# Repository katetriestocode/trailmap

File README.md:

# trailmap
trailmap is a long lasting, gps enabled, e-ink trail map viewer! equipped with temperature, humidity, magnetometer, altitude and gps, it lets the user choose and follow hiking trails like a map! with a usb-c rechargeable lipo battery, it will provide a long lasting and wifi-scarcity proof solution to digital maps :D

this is the working version! (disclaimer: no antenna as it has not delivered yet, so manual gps coords insertion for now!)

provisional 3d model:

pcb:

schematic:

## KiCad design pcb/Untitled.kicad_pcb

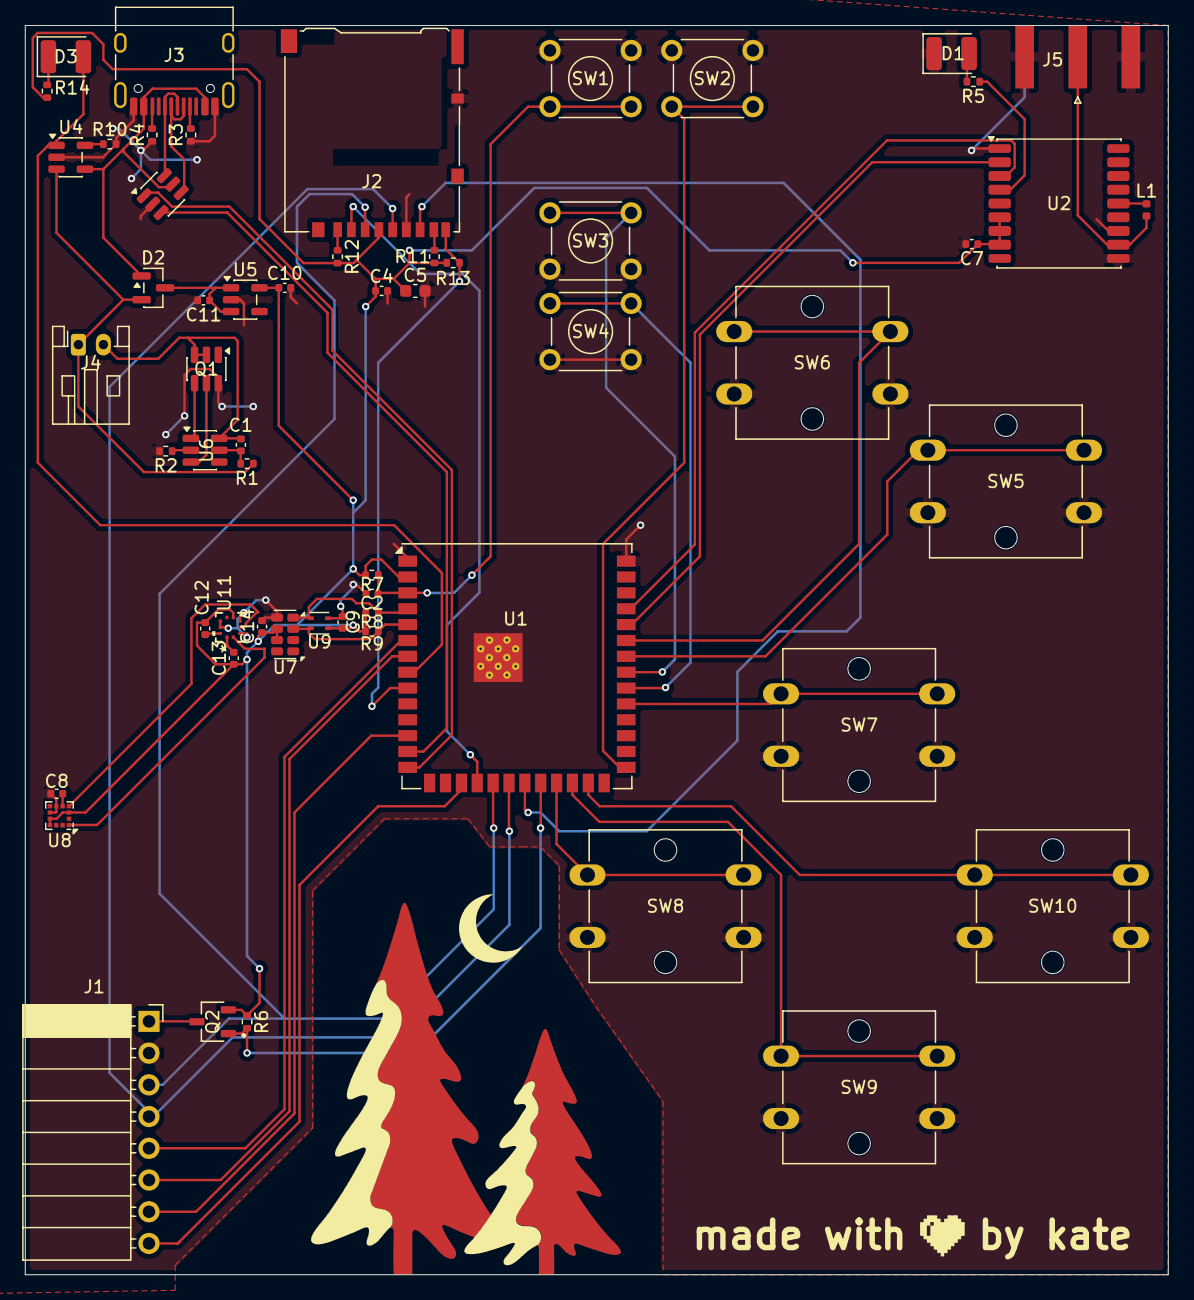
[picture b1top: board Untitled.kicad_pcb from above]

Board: 2 copper layers, 91.5 x 100.0 mm, 57 parts (0 on the bottom side), 53 nets.

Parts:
C1, C4, C7, C9, C14: 0.1uF; C_0402_1005Metric
C2, C10, C11: 1uF; C_0402_1005Metric
C5: 10uF; C_0603_1608Metric
C8: 220nF; C_0402_1005Metric
C12, C13: 0.1UF; C_0402_1005Metric
D1, D3: LED; LED_1210_3225Metric
D2: BAT54C; SOT-23
J1: Conn_01x08_Socket; PinSocket_1x08_P2.54mm_Horizontal
J2: Micro_SD_Card_Det1; microSD_HC_Hirose_DM3AT-SF-PEJM5
J3: USB_C_Receptacle_USB2.0_14P; USB_C_Receptacle_HRO_TYPE-C-31-M-12
J4: Conn_01x02; JST_PH_S2B-PH-K_1x02_P2.00mm_Horizontal
J5: Conn_Coaxial; SMA_Amphenol_132289_EdgeMount
L1: 27nH; L_0402_1005Metric
Q1: FS8205A; SOT-23-6
Q2: AO3407A; SOT95P280X125-3N
R1: 100; R_0402_1005Metric
R2, R5: 1k; R_0402_1005Metric
R3, R4: 5.1k; R_0402_1005Metric
R6, R7, R11, R12, R13: 10k; R_0402_1005Metric
R8, R9: 4.7k; R_0402_1005Metric
R10, R14: 2k; R_0402_1005Metric
SW1: reset; SW_TH_Tactile_Omron_B3F-100x
SW2: boot; SW_TH_Tactile_Omron_B3F-100x
SW3, SW4: SW_Push; SW_TH_Tactile_Omron_B3F-100x
SW5, SW6, SW7, SW8, SW9, SW10: SW_Push; SW_SPST_Omron_B3F-40xx
U1: ESP32-S3-WROOM-1; ESP32-S3-WROOM-1U
U2: MAX-M10S; ublox_MAX
U3: USBLC6-2SC6; SOT-23-6
U4: MCP73831-2-MC; SOT-23-5
U5: AP2112K-3.3; SOT-23-5
U6: DW01A; SOT-23-6
U7: RV-3028-C7; MicroCrystal_C7_SON-8_1.5x3.2mm_P0.9mm
U8: LIS2MDL; LGA-12_2x2mm_P0.5mm
U9: SHT4x; Sensirion_DFN-4_1.5x1.5mm_P0.8mm_SHT4x_NoCentralPad
U11: BMP390; 10LGA_2X2X0p75_BOS

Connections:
+3V3: C4.1, C5.1, C7.1, C9.2, C10.1, C12.1, C13.1, C14.1, J2.4 (VDD), Q2.2, R6.1, R7.1, R8.2, R9.2, R11.2, R12.2, R13.1, R14.1, U1.2 (3V3), U2.6 (V_BCKP), U2.7 (VCC_IO), U2.8 (VCC), U5.5 (VOUT), U7.6 (VBACKUP), U7.7 (VDD), U8.3 (~CS), U8.9 (Vdd), U8.10 (Vdd_IO), U9.3 (VDD), U11.6 (CSB)
+5V: D2.1, J3.A4 (VBUS), J3.A9 (VBUS), J3.B4 (VBUS), J3.B9 (VBUS), U3.5 (VBUS), U4.4 (V_{DD})
BAT+: D2.2, J4.1, R1.1, U4.3 (V_{BAT})
BAT-: C1.2, J4.2, Q1.2, Q1.3, U6.6 (GND)
GND: C2.2, C4.2, C5.2, C7.2, C8.2, C9.1, C10.2, C11.2, C14.2, D1.1 (K), J1.2, J2.6 (VSS), J2.10 (SHIELD), J3.A1 (GND), J3.A12 (GND), J3.B1 (GND), J3.B12 (GND), J5.2 (Ext), Q1.6, R2.2, R3.1, R4.1, R10.2, SW1.1, SW2.1, SW3.2, SW4.2, SW5.2, SW6.2, SW7.2, SW8.2, SW9.2, SW10.2, U1.1 (GND), U1.40 (GND), U1.41 (GND), U2.1 (GND), U2.10 (GND), U2.12 (GND), U3.2 (GND), U4.2 (V_{SS}), U5.2 (GND), U7.5 (VSS), U8.6 (GND), U8.8 (GND), U9.4 (VSS), U11.3 (VSS), U11.5 (SDO), U11.8 (VSS), U11.9 (VSS)
GPS_TO_MCU: U1.36 (RXD0), U2.2 (TXD)
IO06: J1.5, U1.6 (IO6)
IO07: J1.6, U1.7 (IO7)
IO08: J1.7, U1.12 (IO8)
IO09: J1.8, U1.17 (IO9)
IO10: J2.2 (DAT3/CD), U1.18 (IO10)
IO11: J1.3, J2.3 (CMD), U1.19 (IO11)
IO12: J1.4, J2.5 (CLK), U1.20 (IO12)
IO13: J2.7 (DAT0), U1.21 (IO13)
IO14: Q2.1, R6.2, U1.22 (IO14)
IO15: D3.2 (A), U1.8 (IO15), U4.1 (STAT)
IO16: J2.9 (DET), R13.2, U1.9 (IO16)
IO21: SW8.1, U1.23 (IO21)
IO38: SW7.1, U1.31 (IO38)
IO39: SW4.1, U1.32 (IO39)
IO40: SW3.1, U1.33 (IO40)
IO41: SW5.1, U1.34 (IO41)
IO42: SW6.1, U1.35 (IO42)
IO47: SW9.1, U1.24 (IO47)
IO48: SW10.1, U1.25 (IO48)
MCU_TO_GPS: U1.37 (TXD0), U2.3 (RXD)
unnamed: D1.2 (A), R5.2
unnamed: D3.1 (K), R14.2
unnamed: J1.1, Q2.3
unnamed: J2.8 (DAT1), R11.1
unnamed: J2.1 (DAT2), R12.1
unnamed: J3.A5 (CC1), R3.2
unnamed: J3.B5 (CC2), R4.2
unnamed: J3.A6 (D+), J3.B6 (D+), U3.6 (I/O1)
unnamed: J3.A7 (D-), J3.B7 (D-), U3.4 (I/O2)
unnamed: J5.1 (In), L1.2, U2.11 (RF_IN)
unnamed: C2.1, R7.2, SW1.2, U1.3 (EN)
unnamed: SW2.2, U1.27 (IO0)
unnamed: U1.14 (USB_D+), U3.1 (I/O1)
unnamed: U1.13 (USB_D-), U3.3 (I/O2)
unnamed: R5.1, U2.4 (TIMEPULSE)
unnamed: L1.1, U2.14 (VCC_RF)
unnamed: R10.1, U4.5 (PROG)
unnamed: C11.1, D2.3, U5.1 (VIN), U5.3 (EN)
unnamed: R2.1, U6.2 (CS)
unnamed: Q1.5, U6.3 (OC)
unnamed: Q1.4, U6.1 (OD)
unnamed: C1.1, R1.2, U6.5 (VCC)
unnamed: C8.1, U8.5 (C1)
unnamed: C12.2, U11.10 (VDD)
unnamed: C13.2, U11.1 (VDDIO)
SCL: R9.1, U1.5 (IO5), U7.3 (SCL), U8.1 (SCL/SPC), U9.2 (SCL), U11.2 (SCK)
SDA: R8.1, U1.4 (IO4), U7.4 (SDA), U8.4 (SDA/SDI/SDO), U9.1 (SDA), U11.4 (SDI)

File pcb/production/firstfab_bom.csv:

Designator,Footprint,Quantity,Value,LCSC Part #
"C1, C12, C13, C4, C6, C7, C9",0402,7,0.1uF,
"C10, C11, C2",0402,3,1uF,
C5,0603,1,10uF,
C8,0402,1,220nF,
"D1, D3",1210,2,LED,
D2,SOT-23,1,BAT54C,
J1,PinSocket_1x08_P2.54mm_Horizontal,1,Conn_01x08_Socket,
J2,microSD_HC_Hirose_DM3AT-SF-PEJM5,1,Micro_SD_Card_Det1,
J3,USB_C_Receptacle_HRO_TYPE-C-31-M-12,1,USB_C_Receptacle_USB2.0_14P,
J4,JST_PH_S2B-PH-K_1x02_P2.00mm_Horizontal,1,Conn_01x02,
J5,SMA_Amphenol_132289_EdgeMount,1,Conn_Coaxial,
L1,0402,1,27nH,
Q1,SOT-23-6,1,FS8205A,
Q2,SOT95P280X125-3N,1,AO3407A,
R1,0402,1,100,
"R10, R14",0402,2,2k,
"R11, R12, R13, R6, R7",0402,5,10k,
"R2, R5",0402,2,1k,
"R3, R4",0402,2,5.1k,
"R8, R9",0402,2,4.7k,
SW1,SW_TH_Tactile_Omron_B3F-100x,1,reset,
"SW10, SW5, SW6, SW7, SW8, SW9",SW_SPST_Omron_B3F-40xx,6,SW_Push,
SW2,SW_TH_Tactile_Omron_B3F-100x,1,boot,
"SW3, SW4",SW_TH_Tactile_Omron_B3F-100x,2,SW_Push,
U1,ESP32-S3-WROOM-1U,1,ESP32-S3-WROOM-1,
U10,IC_RV-3028-C8-32.768KHZ-1PPM-TA-QC,1,RV-3028-C8-32.768KHZ-1PPM-TA-QC,
U11,10LGA_2X2X0p75_BOS,1,BMP390,
U2,ublox_MAX,1,MAX-M10S,
U3,SOT-23-6,1,USBLC6-2SC6,
U4,SOT-23-5,1,MCP73831-2-MC,
U5,SOT-23-5,1,AP2112K-3.3,
U6,SOT-23-6,1,DW01A,
U8,LGA-12_2x2mm_P0.5mm,1,LIS2MDL,
U9,Sensirion_DFN-4_1.5x1.5mm_P0.8mm_SHT4x_NoCentralPad,1,SHT4x,

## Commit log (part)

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2026-06-17 boop
2026-06-26 bump
2026-06-29 schematic
2026-06-29 journal
2026-06-29 journal update
2026-06-30 new?
2026-06-30 journal!
